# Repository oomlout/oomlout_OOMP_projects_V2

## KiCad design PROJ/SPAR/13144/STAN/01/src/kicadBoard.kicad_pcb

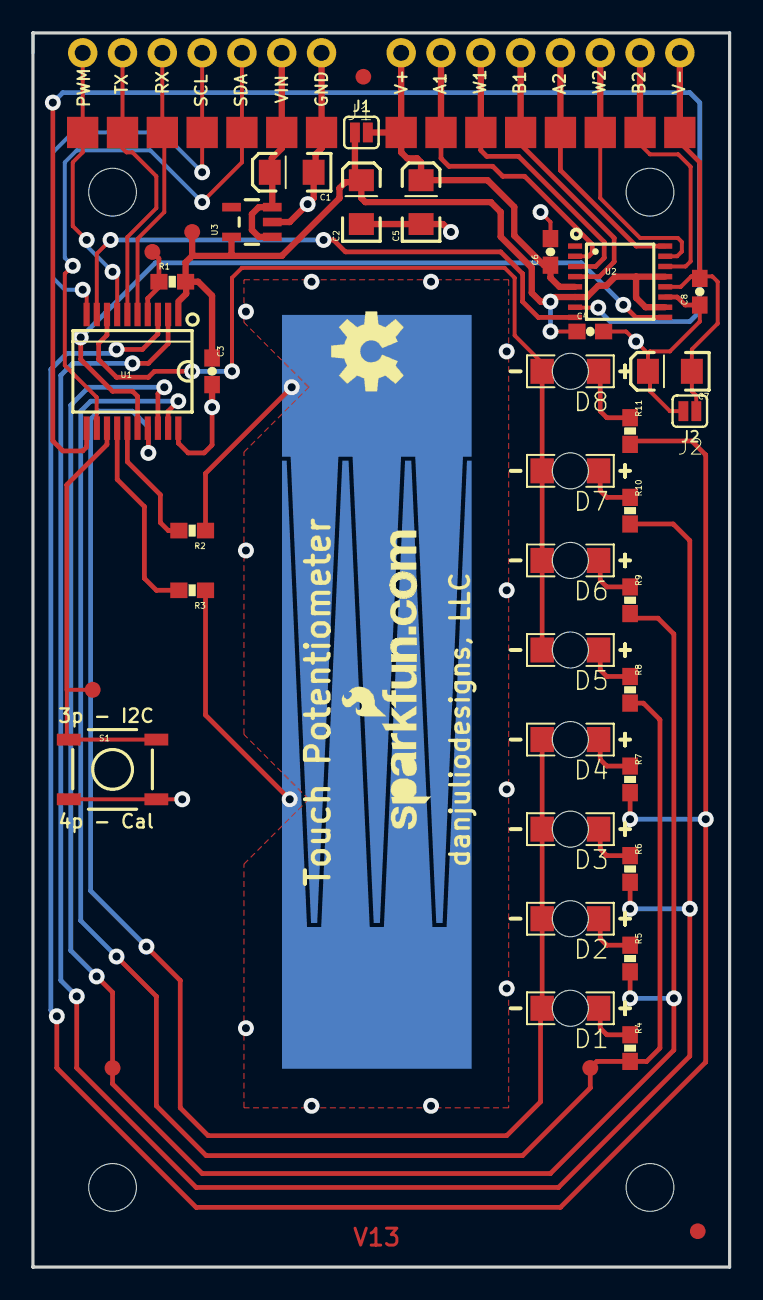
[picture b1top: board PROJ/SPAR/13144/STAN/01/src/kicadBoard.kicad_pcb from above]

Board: 2 copper layers, 44.5 x 78.7 mm, 78 parts (1 on the bottom side), 39 nets.

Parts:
C1, C2, C5, C7: 10uF; EIA3216
C3, C4, C6, C8: 0.1uF; 0603-CAP
D1, D2, D3, D4, D5, D6, D7, D8: Green; LED-1206-BOTTOM
FID1, FID2: FIDUCIAL1X2; FIDUCIAL-1X2
FRAME3: FRAME-LEDGER; CREATIVE_COMMONS
J1, J2: SJ_2S
JP1, JP2, JP3, JP4, JP5, JP6, JP7, JP8, JP9, JP10, JP11, JP12, JP13, JP14, JP15: 1X01NS
R1: 10K; 0603-RES
R2, R3, R4, R5, R6, R7, R8, R9, R10, R11: 100; 0603-RES
S1: TACTILE-SWITCH-SMD
STANDOFF1, STANDOFF2, STANDOFF3, STANDOFF4: STAND-OFFTIGHT; STAND-OFF-TIGHT
TP1, TP2, TP3, TP4, TP5: PAD.03X.04
TP6, TP7, TP8, TP9, TP10, TP11, TP12, TP13, TP14, TP15, TP16, TP17, TP18, TP19, TP20: 2MM_SMD_PAD
TS1: 2CH_48MM_LINEAR_TOUCH
U1: PIC16F1829; SSOP20
U2: AD5262; SSOP16
U3: 5V; SOT23-5
U$4: OSHW-LOGOM; OSHW-LOGO-M
U$5: SFE_LOGO_NAME_WEB; SFE-NEW-WEBLOGO

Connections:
+5V: C2.A, C3.1, C4.1, J1.1, R1.2, TP2.P$1, U1.1, U2.6, U2.10, U2.13, U3.5
A1: JP14.1, TP19.P$1, U2.2
A2: JP11.1, TP16.P$1, U2.16
AUX: S1.1, TP3.P$1, U1.13
B1: JP12.1, TP17.P$1, U2.4
B2: JP9.1, TP14.P$1, U2.14
CPAD1: R3.2, U1.14
CPAD2: R2.2, U1.15
CSN: U1.16, U2.9
GND: C1.C, C2.C, C3.2, C4.2, C5.C, C6.2, C7.A, C8.1, J2.1, JP7.1, S1.3, TP12.P$1, U1.20, U2.11, U3.2
LA0: R4.2, R8.2, TP4.P$1, U1.19
LA1: R5.2, R9.2, TP5.P$1, U1.18
LA2: R6.2, R10.2, U1.2
LA3: R7.2, R11.2, U1.3
LED_PWM1: D1.C, D2.C, D3.C, D4.C, U1.17
LED_PWM2: D5.C, D6.C, D7.C, D8.C, U1.8
unnamed: D1.A, R4.1
unnamed: D2.A, R5.1
unnamed: D3.A, R6.1
unnamed: D4.A, R7.1
unnamed: D5.A, R8.1
unnamed: D6.A, R9.1
unnamed: D7.A, R10.1
unnamed: D8.A, R11.1
unnamed: R2.1, TS1.P$2
unnamed: R3.1, TS1.P$1
PWM_OUT: JP3.1, TP8.P$1, U1.7
RX: JP4.1, TP9.P$1, U1.5
SCL: JP2.1, TP7.P$1, U1.10
SCLK: U1.11, U2.7
SDA: JP1.1, TP6.P$1, U1.12
SDO: U1.9, U2.8
TX: JP5.1, TP10.P$1, U1.6
V+: C5.A, C6.1, J1.2, JP15.1, TP20.P$1, U2.5
V-: C7.C, C8.2, J2.2, JP8.1, TP13.P$1, U2.12
VIN: C1.A, JP6.1, TP11.P$1, U3.1, U3.3
VPP: R1.1, TP1.P$1, U1.4
W1: JP13.1, TP18.P$1, U2.3
W2: JP10.1, TP15.P$1, U2.15

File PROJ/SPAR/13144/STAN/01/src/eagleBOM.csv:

"Part";"Value";"Device";"Package";"Description";"PROD_ID";"VALUE";
"C1";"10uF";"10UF-16V-10%(TANT)";"EIA3216";"CAP-00811";"CAP-00811";"10uF";
"C2";"10uF";"10UF-16V-10%(TANT)";"EIA3216";"CAP-00811";"CAP-00811";"10uF";
"C3";"0.1uF";"0.1UF-25V(+80/-20%)(0603)";"0603-CAP";"CAP-00810";"CAP-00810";"0.1uF";
"C4";"0.1uF";"0.1UF-25V(+80/-20%)(0603)";"0603-CAP";"CAP-00810";"CAP-00810";"0.1uF";
"C5";"10uF";"10UF-16V-10%(TANT)";"EIA3216";"CAP-00811";"CAP-00811";"10uF";
"C6";"0.1uF";"0.1UF-25V(+80/-20%)(0603)";"0603-CAP";"CAP-00810";"CAP-00810";"0.1uF";
"C7";"10uF";"10UF-16V-10%(TANT)";"EIA3216";"CAP-00811";"CAP-00811";"10uF";
"C8";"0.1uF";"0.1UF-25V(+80/-20%)(0603)";"0603-CAP";"CAP-00810";"CAP-00810";"0.1uF";
"D1";"Green";"LED-GREEN1206-BOTTOM";"LED-1206-BOTTOM";"Various green LEDs";"DIO-11076";"Green";
"D2";"Green";"LED-GREEN1206-BOTTOM";"LED-1206-BOTTOM";"Various green LEDs";"DIO-11076";"Green";
"D3";"Green";"LED-GREEN1206-BOTTOM";"LED-1206-BOTTOM";"Various green LEDs";"DIO-11076";"Green";
"D4";"Green";"LED-GREEN1206-BOTTOM";"LED-1206-BOTTOM";"Various green LEDs";"DIO-11076";"Green";
"D5";"Green";"LED-GREEN1206-BOTTOM";"LED-1206-BOTTOM";"Various green LEDs";"DIO-11076";"Green";
"D6";"Green";"LED-GREEN1206-BOTTOM";"LED-1206-BOTTOM";"Various green LEDs";"DIO-11076";"Green";
"D7";"Green";"LED-GREEN1206-BOTTOM";"LED-1206-BOTTOM";"Various green LEDs";"DIO-11076";"Green";
"D8";"Green";"LED-GREEN1206-BOTTOM";"LED-1206-BOTTOM";"Various green LEDs";"DIO-11076";"Green";
"FID1";"FIDUCIAL1X2";"FIDUCIAL1X2";"FIDUCIAL-1X2";"Fiducial Alignment Points";"";"";
"FID2";"FIDUCIAL1X2";"FIDUCIAL1X2";"FIDUCIAL-1X2";"Fiducial Alignment Points";"";"";
"FRAME3";"FRAME-LEDGER";"FRAME-LEDGER";"CREATIVE_COMMONS";"Schematic Frame";"";"";
"J1";"";"SJCLOSED";"SJ_2S";"Solder jumper";"";"";
"J2";"";"SJCLOSED";"SJ_2S";"Solder jumper";"";"";
"JP1";"";"M01SMDNS";"1X01NS";"Header 1";"";"";
"JP2";"";"M01SMDNS";"1X01NS";"Header 1";"";"";
"JP3";"";"M01SMDNS";"1X01NS";"Header 1";"";"";
"JP4";"";"M01SMDNS";"1X01NS";"Header 1";"";"";
"JP5";"";"M01SMDNS";"1X01NS";"Header 1";"";"";
"JP6";"";"M01SMDNS";"1X01NS";"Header 1";"";"";
"JP7";"";"M01SMDNS";"1X01NS";"Header 1";"";"";
"JP8";"";"M01SMDNS";"1X01NS";"Header 1";"";"";
"JP9";"";"M01SMDNS";"1X01NS";"Header 1";"";"";
"JP10";"";"M01SMDNS";"1X01NS";"Header 1";"";"";
"JP11";"";"M01SMDNS";"1X01NS";"Header 1";"";"";
"JP12";"";"M01SMDNS";"1X01NS";"Header 1";"";"";
"JP13";"";"M01SMDNS";"1X01NS";"Header 1";"";"";
"JP14";"";"M01SMDNS";"1X01NS";"Header 1";"";"";
"JP15";"";"M01SMDNS";"1X01NS";"Header 1";"";"";
"R1";"10K";"10KOHM-1/10W-1%(0603)0603";"0603-RES";"RES-00824";"RES-00824";"10K";
"R2";"100";"100OHM-1/10W-1%(0603)";"0603-RES";"RES-07863";"RES-07863";"100";
"R3";"100";"100OHM-1/10W-1%(0603)";"0603-RES";"RES-07863";"RES-07863";"100";
"R4";"100";"100OHM-1/10W-1%(0603)";"0603-RES";"RES-07863";"RES-07863";"100";
"R5";"100";"100OHM-1/10W-1%(0603)";"0603-RES";"RES-07863";"RES-07863";"100";
"R6";"100";"100OHM-1/10W-1%(0603)";"0603-RES";"RES-07863";"RES-07863";"100";
"R7";"100";"100OHM-1/10W-1%(0603)";"0603-RES";"RES-07863";"RES-07863";"100";
"R8";"100";"100OHM-1/10W-1%(0603)";"0603-RES";"RES-07863";"RES-07863";"100";
"R9";"100";"100OHM-1/10W-1%(0603)";"0603-RES";"RES-07863";"RES-07863";"100";
"R10";"100";"100OHM-1/10W-1%(0603)";"0603-RES";"RES-07863";"RES-07863";"100";
"R11";"100";"100OHM-1/10W-1%(0603)";"0603-RES";"RES-07863";"RES-07863";"100";
"S1";"";"SWITCH-MOMENTARY-2SMD";"TACTILE-SWITCH-SMD";"Various NO switches- pushbuttons, reed, etc";"SWCH-08247";"";
"STANDOFF1";"STAND-OFFTIGHT";"STAND-OFFTIGHT";"STAND-OFF-TIGHT";"#4 Stand Off";"";"";
"STANDOFF2";"STAND-OFFTIGHT";"STAND-OFFTIGHT";"STAND-OFF-TIGHT";"#4 Stand Off";"";"";
"STANDOFF3";"STAND-OFFTIGHT";"STAND-OFFTIGHT";"STAND-OFF-TIGHT";"#4 Stand Off";"";"";
"STANDOFF4";"STAND-OFFTIGHT";"STAND-OFFTIGHT";"STAND-OFF-TIGHT";"#4 Stand Off";"";"";
"TP1";"";"TEST-POINT3X4";"PAD.03X.04";"Bare copper test points for troubleshooting or ICT";"";"";
"TP2";"";"TEST-POINT3X4";"PAD.03X.04";"Bare copper test points for troubleshooting or ICT";"";"";
"TP3";"";"TEST-POINT3X4";"PAD.03X.04";"Bare copper test points for troubleshooting or ICT";"";"";
"TP4";"";"TEST-POINT3X4";"PAD.03X.04";"Bare copper test points for troubleshooting or ICT";"";"";
"TP5";"";"TEST-POINT3X4";"PAD.03X.04";"Bare copper test points for troubleshooting or ICT";"";"";
"TP6";"";"SINGLE_PADSMD";"2MM_SMD_PAD";"";"";"";
"TP7";"";"SINGLE_PADSMD";"2MM_SMD_PAD";"";"";"";
"TP8";"";"SINGLE_PADSMD";"2MM_SMD_PAD";"";"";"";
"TP9";"";"SINGLE_PADSMD";"2MM_SMD_PAD";"";"";"";
"TP10";"";"SINGLE_PADSMD";"2MM_SMD_PAD";"";"";"";
"TP11";"";"SINGLE_PADSMD";"2MM_SMD_PAD";"";"";"";
"TP12";"";"SINGLE_PADSMD";"2MM_SMD_PAD";"";"";"";
"TP13";"";"SINGLE_PADSMD";"2MM_SMD_PAD";"";"";"";
"TP14";"";"SINGLE_PADSMD";"2MM_SMD_PAD";"";"";"";
"TP15";"";"SINGLE_PADSMD";"2MM_SMD_PAD";"";"";"";
"TP16";"";"SINGLE_PADSMD";"2MM_SMD_PAD";"";"";"";
"TP17";"";"SINGLE_PADSMD";"2MM_SMD_PAD";"";"";"";
"TP18";"";"SINGLE_PADSMD";"2MM_SMD_PAD";"";"";"";
"TP19";"";"SINGLE_PADSMD";"2MM_SMD_PAD";"";"";"";
"TP20";"";"SINGLE_PADSMD";"2MM_SMD_PAD";"";"";"";
"TS1";"";"2CH_LINEAR_TOUCH";"2CH_48MM_LINEAR_TOUCH";"";"";"";
"U$4";"OSHW-LOGOM";"OSHW-LOGOM";"OSHW-LOGO-M";"Open Source Hardware Logo This logo indicates the piece of hardware it is found on incorporates a OSHW license and/or adheres to the definition of open source hardware found here: http://freedomdefined.org/OSHW";"";"";
"U$5";"SFE_LOGO_NAME_WEB";"SFE_LOGO_NAME_WEB";"SFE-NEW-WEBLOGO";"SparkFun.com board silk.";"";"";
"U1";"PIC16F1829";"PIC16F1829";"SSOP20";"";"IC-12357";"";
"U2";"AD5262";"AD5262";"SSOP16";"";"IC-12358";"";
"U3";"5V";"V_REG_MIC52055V";"SOT23-5";"V_REG MIC5219";"VREG-00823";"5V";

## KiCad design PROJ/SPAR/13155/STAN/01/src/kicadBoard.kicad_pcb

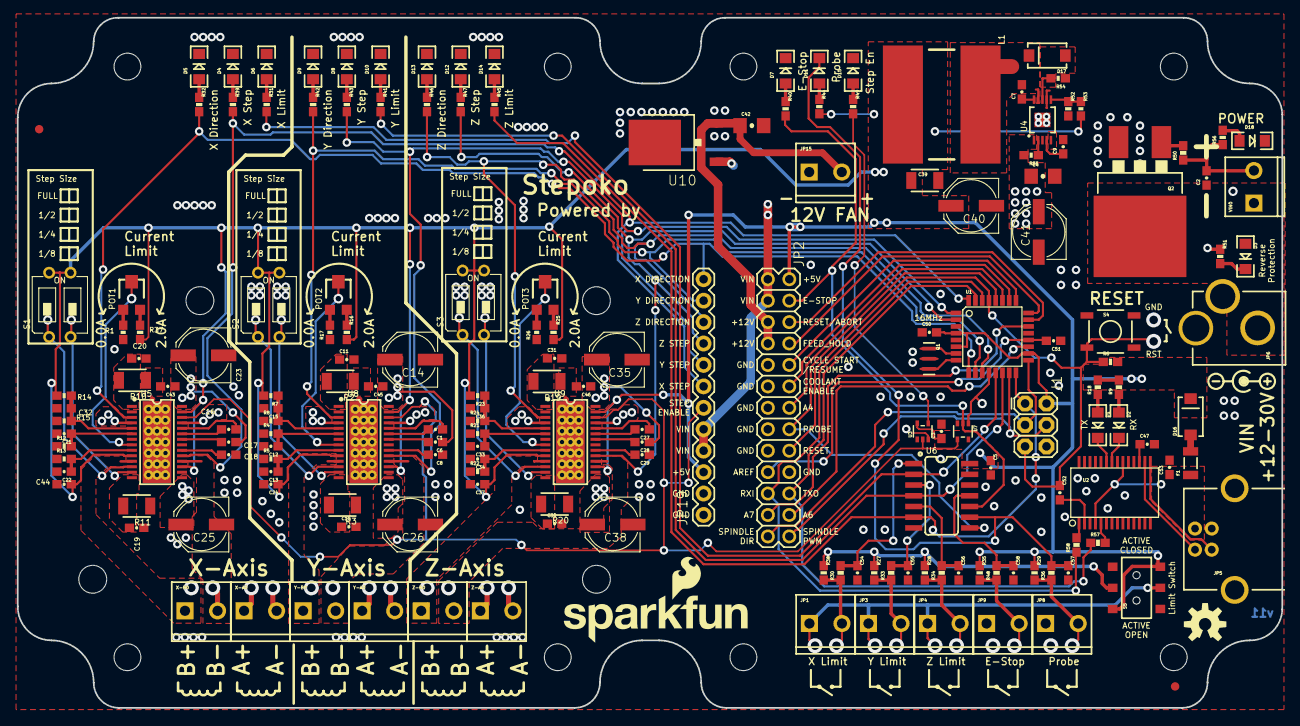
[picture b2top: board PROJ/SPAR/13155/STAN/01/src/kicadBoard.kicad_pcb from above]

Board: 2 copper layers, 149.9 x 81.8 mm, 184 parts (1 on the bottom side), 133 nets.

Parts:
C1, C6, C8, C16, C17, C18, C27, C28, C29: 0.22uF; 0603-CAP
C2, C3, C5, C7, C10, C11, C19, C20, C24, C30, C31, C37, C43, C44, C45, C46, C47, C50, C51, C52, C53, C54, C55, C56, C57, C58: 0.1uF; 0603-CAP
C4, C42: 1.0uF; 1206-CAP
C9: 10nF; 0603-CAP
C12, C13, C21, C22, C33, C34: 1nF; 0603-CAP
C14, C23, C25, C26, C35, C38, C40, C41: 47uF; PANASONIC_D
C15, C32, C36: 0.18uF; 0603
C39: 22uF; 1210
D1, D3, D5, D7, D9, D13: RED; LED-1206
D2, D4, D8, D12, D15: GREEN; LED-1206
D6, D10, D14: Yellow; LED-1206
D11, D18: BLUE; LED-1206
D16, D17: MBRA140; SMA-DIODE
F1: PTCSMD; PTC-1206
FID1, FID2: FIDUCIAL1X2; FIDUCIAL-1X2
FRAME1, FRAME2: FRAME-LEDGER; CREATIVE_COMMONS
J1: AVR ISP; 2X3
JP1, JP3, JP4, JP8, JP9, JP15: 3.5mm; SCREWTERMINAL-3.5MM-2_LOCK
JP2: 2X13
JP5: USB-B; USB-B-PTH
JP6: POWER; POWER_JACK_PTH_LOCK
JP19: 1X12
L1: 27uH; INDUCTOR_SDR1307
LOGO1: OSHW-LOGOM; OSHW-LOGO-M
LOGO2: SFE_LOGO_NAME_FLAME.2_INCH; SFE_LOGO_NAME_FLAME_.2@1
LOGO3: SFE_LOGO_NAME_FLAME.2_INCH; SFE_LOGO_NAME_FLAME_.2
POT1, POT2, POT3: 10K_LINEAR_POT_SMD; TC33X
Q1: 16MHZ; RESONATOR-SMD
Q2: 100A/100V; TO-263_D2PAK
R1, R17, R26: 0; 0603
R2, R3, R10, R11, R19, R20: 0.1; 1210
R4, R5, R12, R13, R21, R22: 39K; 0603
R6, R16, R25, R27, R28, R29, R35, R37, R38, R51, R52, R56: 10K; 0603-RES
R7, R8, R14, R15, R23, R24: 5.6K; 0603
R9, R18, R30, R33, R34, R36, R48, R50, R57, R58: 1K; 0603-RES@1
R31, R32, R39, R40, R41, R42, R43, R44, R45, R46, R47, R49: 1K; 0603-RES
R53: 9.76K; 0603
R54: 50.0m; 0603
R55: 348K; 0603
S1, S2, S3: 2-POS-DIPCTS-THRU-HOLE; 209-2LPST
S4: Reset; TACTILE-SWITCH-SMD
S5: DPDT; AYZ0202
U1: ATMEGA328; TQFP32-08@1
U2: FT232RLSSOP; SSOP28DB
U3: 74LVC1G04; SOT353
U4: LM25011; HVSS0P-10
U5, U8, U9: DRV8811; HTSSOP28
U6: 74HC7014D; SOIC-14
U7: 7432SE; SOT353
U10: +12v; TO-252
U$1: FLANGED_RED_ENCLOSURE-DIMENSION-NO-INNER-HOLES
U$2, U$3, U$4, U$5: STAND-OFF
VIN0: 3.5mm; SCREWTERMINAL-3.5MM-2_LOCK
X-A0: 3.5mm; SCREWTERMINAL-3.5MM-2_LOCK
X-B0: 3.5mm; SCREWTERMINAL-3.5MM-2_LOCK
Y-A0: 3.5mm; SCREWTERMINAL-3.5MM-2_LOCK
Y-B0: 3.5mm; SCREWTERMINAL-3.5MM-2_LOCK
Z-A0: 3.5mm; SCREWTERMINAL-3.5MM-2_LOCK
Z-B0: 3.5mm; SCREWTERMINAL-3.5MM-2_LOCK

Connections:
5V: C3.1, C5.1, C24.1, C37.1, C39.1, C40.+, C44.1, C50.2, D16.C, J1.2, JP2.2, JP19.3, L1.P$2, R6.2, R7.2, R9.2, R14.2, R16.2, R18.2, R23.2, R25.2, R29.1, R35.1, R37.2, R44.2, R53.2, S1.3, S1.4, S2.3, S2.4, S3.3, S3.4, S5.1, S5.6, U1.4, U1.6, U1.18, U3.5, U5.10, U5.17, U5.27, U6.14, U7.5, U8.10, U8.17, U8.27, U9.10, U9.17, U9.27
A0-RESET/ABORT: JP2.6, U1.23
A1-FEED_HOLD: JP2.8, U1.24
A2-CYCLE_START/RESUME: JP2.10, U1.25
A3-COOLANT_ENABLE: JP2.12, U1.26
A4: JP2.14, U1.27
A5-PROBE: JP2.16, U1.28, U6.8
A6: JP2.24, U1.19
A7: JP2.23, U1.22
AREF: C51.2, JP2.19, U1.20
D2-STEP-X: JP19.7, R39.2, U1.32, U5.19
D3-STEP-Y: JP19.8, R43.2, U1.1, U8.19
D4-STEP-Z: JP19.9, R47.2, U1.2, U9.19
D5-DIR-X: JP19.12, R32.2, U1.9, U5.3
D6-DIR-Y: JP19.11, R42.2, U1.10, U8.3
D7-DIR-Z: JP19.10, R46.2, U1.11, U9.3
D8-STEP_EN: U1.12, U7.1
D9-LIM-X: R31.2, U1.13, U6.2
D10-LIM-Y: R41.2, U1.14, U6.4
D+: JP5.D+, U2.15
D-: JP5.D-, U2.16
DTR: C52.2, U2.2
ESTOP: C58.1, R48.2, U6.11
ESTOP-LOGIC: JP2.4, R40.2, U6.10, U7.2
GND: C3.2, C4.2, C5.2, C8.1, C9.2, C10.2, C11.2, C12.2, C13.2, C14.-, C15.2, C18.1, C19.2, C20.2, C21.2, C22.2, C23.-, C24.2, C25.-, C26.-, C29.1, C30.2, C31.2, C32.2, C33.2, C34.2, C35.-, C36.2, C37.2, C38.-, C39.2, C40.-, C41.-, C42.2, C43.2, C44.2, C45.2, C46.2, C47.2, C50.1, C51.1, C53.2, C54.2, C55.2, C56.2, C57.2, C58.2, D4.C, D5.C, D6.C, D7.C, D8.C, D9.C, D10.C, D12.C, D13.C, D14.C, D15.C, D18.C, J1.6, JP2.9, JP2.11, JP2.13, JP2.15, JP2.17, JP2.20, JP5.GND, JP8.1, JP9.1, JP15.1, JP19.1, JP19.2, Q1.2, Q2.3, R1.1, R2.1, R3.1, R4.1, R5.1, R8.1, R10.1, R11.1, R12.1, R13.1, R15.1, R17.1, R19.1, R20.1, R21.1, R22.1, R24.1, R26.1, R52.2, R54.1, S4.1, S5.3, S5.4, U1.3, U1.5, U1.21, U2.7, U2.18, U2.21, U2.25, U2.26, U3.3, U4.5, U4.7, U4.PAD, U5.7, U5.16, U5.21, U5.GND@10, U5.GND@11, U5.GND@12, U5.GND@13, U5.GND@14, U5.GND@15, U5.GND@16, U5.GND@17, U5.GND@18, U5.GND@19, U5.GND@20, U5.GND@21, U5.GND@22, U5.GND@23, U5.GND@24, U5.GND@25, U5.GND@26, U5.GND@27, U5.GND@28, U5.GND@29, U5.GND@30, U5.GND@PAD, U6.7, U6.13, U7.3, U8.7, U8.16, U8.21, U8.GND@10, U8.GND@11, U8.GND@12, U8.GND@13, U8.GND@14, U8.GND@15, U8.GND@16, U8.GND@17, U8.GND@18, U8.GND@19, U8.GND@20, U8.GND@21, U8.GND@22, U8.GND@23, U8.GND@24, U8.GND@25, U8.GND@26, U8.GND@27, U8.GND@28, U8.GND@29, U8.GND@30, U8.GND@PAD, U9.7, U9.16, U9.21, U9.GND@10, U9.GND@11, U9.GND@12, U9.GND@13, U9.GND@14, U9.GND@15, U9.GND@16, U9.GND@17, U9.GND@18, U9.GND@19, U9.GND@20, U9.GND@21, U9.GND@22, U9.GND@23, U9.GND@24, U9.GND@25, U9.GND@26, U9.GND@27, U9.GND@28, U9.GND@29, U9.GND@30, U9.GND@PAD, U10.3
MISO-D12-LIMIT-Z: J1.1, R45.2, U1.16, U6.6
MOSI-D11-SPINDLE_PWM: J1.4, JP2.26, U1.15
unnamed: R58.2, U2.1
unnamed: D2.A, R9.1
unnamed: D1.A, R18.1
unnamed: JP1.1, JP3.1, JP4.1, S5.5
unnamed: D7.A, R40.1
unnamed: Q1.3, U1.8
unnamed: JP1.2, R30.1, R38.2
unnamed: Q1.1, U1.7
unnamed: POT1.3, R37.1
unnamed: POT1.1, R1.2
unnamed: C12.1, R4.2, U8.6
unnamed: C13.1, R5.2, U8.9
unnamed: D11.A, R44.1
unnamed: C15.1, R7.1, R8.2, U8.5
unnamed: S2.2, U8.13
unnamed: D15.A, R49.1
unnamed: C2.1, D3.A, JP6.GND, Q2.2, VIN0.1
unnamed: D6.A, R31.1
unnamed: D5.A, R32.1
unnamed: D4.A, R39.1
unnamed: R52.1, R53.1, U4.6
unnamed: D10.A, R41.1
unnamed: S2.1, U8.12
unnamed: C16.1, U5.24
unnamed: C16.2, U5.23
unnamed: C8.2, U8.20
unnamed: POT2.2, U8.8
unnamed: C21.1, R12.2, U5.6
unnamed: C22.1, R13.2, U5.9
unnamed: C32.1, R14.1, R15.2, U5.5
unnamed: D9.A, R42.1
unnamed: D1.C, U2.23
unnamed: D2.C, U2.22
unnamed: S1.2, U5.13
unnamed: S1.1, U5.12
unnamed: D8.A, R43.1
unnamed: U5.11, X-B0.1
unnamed: C18.2, U5.20
unnamed: Q2.1, R50.2
unnamed: D14.A, R45.1
unnamed: D3.C, R51.2
unnamed: JP3.2, R27.2, R33.1
unnamed: JP4.2, R28.2, R34.1
unnamed: POT2.3, R16.1
unnamed: POT2.1, R17.2
unnamed: C6.2, U8.22
unnamed: C1.1, U8.24
unnamed: C1.2, U8.23
unnamed: U8.11, Y-B0.1
unnamed: D16.A, F1.2
unnamed: JP8.2, R29.2, R36.1
unnamed: U8.18, Y-B0.2
unnamed: U8.4, Y-A0.1
unnamed: JP9.2, R35.2, R48.1
unnamed: U8.25, Y-A0.2
unnamed: C10.1, R3.2, U8.14
unnamed: D18.A, R56.2
unnamed: D13.A, R46.1
unnamed: D12.A, R47.1
unnamed: R57.2, U2.5
unnamed: R55.1, U4.2
unnamed: C17.2, U5.22
unnamed: C7.1, U4.10
unnamed: U5.18, X-B0.2
unnamed: C7.2, D17.C, L1.P$1, U4.9
unnamed: U5.4, X-A0.1
unnamed: C11.1, R2.2, U8.1
unnamed: C33.1, R21.2, U9.6
unnamed: C34.1, R22.2, U9.9
unnamed: C36.1, R23.1, R24.2, U9.5
unnamed: S3.2, U9.13
unnamed: S3.1, U9.12
unnamed: C9.1, U4.4
unnamed: U5.25, X-A0.2
unnamed: C29.2, U9.20
unnamed: POT3.2, U9.8
unnamed: POT3.3, R25.1
unnamed: POT3.1, R26.2
unnamed: C28.2, U9.22
unnamed: C27.1, U9.24
unnamed: C27.2, U9.23
unnamed: U9.11, Z-B0.1
unnamed: U9.18, Z-B0.2
unnamed: U9.4, Z-A0.1
unnamed: U9.25, Z-A0.2
unnamed: C30.1, R20.2, U9.14
unnamed: C19.1, R11.2, U5.14
unnamed: C31.1, R19.2, U9.1
unnamed: POT1.2, U5.8
unnamed: R27.1, R28.1, R38.1, S5.2
unnamed: C20.1, R10.2, U5.1
unnamed: D17.A, R54.2, U4.8
unnamed: C47.1, U2.17
PROBE: C57.1, D11.C, R36.2, U6.9
RESET: C52.1, J1.5, JP2.18, R6.1, S4.3, U1.29
RXI: JP2.21, R58.1, U1.30
SCK-D13-SPINDLE_DIR: J1.3, JP2.25, U1.17
STEP-EN_LED: R49.2, U3.4
STEP_ENABLE: JP19.6, U3.2, U5.26, U7.4, U8.26, U9.26
TXO: JP2.22, R57.1, U1.31
VCC: C42.1, JP2.5, JP2.7, JP15.2, U10.2
VCC_USB: C53.1, F1.1, JP5.VBUS, U2.4, U2.20
VIN: C2.2, C4.1, C6.1, C14.+, C17.1, C23.+, C25.+, C26.+, C28.1, C35.+, C38.+, C41.+, C43.1, C45.1, C46.1, JP2.1, JP2.3, JP6.PWR, JP19.4, JP19.5, R50.1, R51.1, R55.2, R56.1, U4.1, U5.15, U5.28, U8.15, U8.28, U9.15, U9.28, U10.1, VIN0.2
X_LIM: C54.1, R30.2, U6.1
Y_LIM: C55.1, R33.2, U6.3
Z_LIM: C56.1, R34.2, U6.5

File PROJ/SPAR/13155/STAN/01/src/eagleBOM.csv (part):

"Part";"Value";"Device";"Package";"Description";"DESIGNER";"PROD_ID";"SF_ID";"VALUE";"VERSION";
"C1";"0.22uF";"0.22UF50V-20%,+80%(0603)";"0603-CAP";"CAP-09885";"";"CAP-09885";"";"0.22uF";"";
"C2";"0.1uF";"0.1UF-100V-10%(0603)";"0603-CAP";"CAP-08390";"";"CAP-08390";"";"0.1uF";"";
"C3";"0.1uF";"0.1UF-25V(+80/-20%)(0603)";"0603-CAP";"CAP-00810";"";"CAP-00810";"";"0.1uF";"";
"C4";"1.0uF";"1.0UF50V10%(1206)";"1206-CAP";"CAP-09822";"";"";"";"";"";
"C5";"0.1uF";"0.1UF-25V(+80/-20%)(0603)";"0603-CAP";"CAP-00810";"";"CAP-00810";"";"0.1uF";"";
"C6";"0.22uF";"0.22UF50V-20%,+80%(0603)";"0603-CAP";"CAP-09885";"";"CAP-09885";"";"0.22uF";"";
"C7";"0.1uF";"0.1UF-25V(+80/-20%)(0603)";"0603-CAP";"CAP-00810";"";"CAP-00810";"";"0.1uF";"";
"C8";"0.22uF";"0.22UF50V-20%,+80%(0603)";"0603-CAP";"CAP-09885";"";"CAP-09885";"";"0.22uF";"";
"C9";"10nF";"10NF/10000PF-50V-10%(0603)";"0603-CAP";"CAP-00867";"";"CAP-00867";"";"10nF";"";
"C10";"0.1uF";"0.1UF-25V(+80/-20%)(0603)";"0603-CAP";"CAP-00810";"";"CAP-00810";"";"0.1uF";"";
"C11";"0.1uF";"0.1UF-25V(+80/-20%)(0603)";"0603-CAP";"CAP-00810";"";"CAP-00810";"";"0.1uF";"";
"C12";"1nF";"1NF/1000PF-50V-10%(0603)";"0603-CAP";"CAP-07886";"";"CAP-07886";"";"1nF";"";
"C13";"1nF";"1NF/1000PF-50V-10%(0603)";"0603-CAP";"CAP-07886";"";"CAP-07886";"";"1nF";"";
"C14";"47uF";"47UF-50V-20%(ELECT)";"PANASONIC_D";"CAP-10547";"";"CAP-10547";"";"";"";
"C15";"0.18uF";"0.18UF-10V(+-10%)(0603)";"0603";"";"";"CAP-12380";"";"";"";
"C16";"0.22uF";"0.22UF50V-20%,+80%(0603)";"0603-CAP";"CAP-09885";"";"CAP-09885";"";"0.22uF";"";
"C17";"0.22uF";"0.22UF50V-20%,+80%(0603)";"0603-CAP";"CAP-09885";"";"CAP-09885";"";"0.22uF";"";
"C18";"0.22uF";"0.22UF50V-20%,+80%(0603)";"0603-CAP";"CAP-09885";"";"CAP-09885";"";"0.22uF";"";
"C19";"0.1uF";"0.1UF-25V(+80/-20%)(0603)";"0603-CAP";"CAP-00810";"";"CAP-00810";"";"0.1uF";"";
"C20";"0.1uF";"0.1UF-25V(+80/-20%)(0603)";"0603-CAP";"CAP-00810";"";"CAP-00810";"";"0.1uF";"";
"C21";"1nF";"1NF/1000PF-50V-10%(0603)";"0603-CAP";"CAP-07886";"";"CAP-07886";"";"1nF";"";
"C22";"1nF";"1NF/1000PF-50V-10%(0603)";"0603-CAP";"CAP-07886";"";"CAP-07886";"";"1nF";"";
"C23";"47uF";"47UF-50V-20%(ELECT)";"PANASONIC_D";"CAP-10547";"";"CAP-10547";"";"";"";
"C24";"0.1uF";"0.1UF-25V(+80/-20%)(0603)";"0603-CAP";"CAP-00810";"";"CAP-00810";"";"0.1uF";"";
"C25";"47uF";"47UF-50V-20%(ELECT)";"PANASONIC_D";"CAP-10547";"";"CAP-10547";"";"";"";
"C26";"47uF";"47UF-50V-20%(ELECT)";"PANASONIC_D";"CAP-10547";"";"CAP-10547";"";"";"";
"C27";"0.22uF";"0.22UF50V-20%,+80%(0603)";"0603-CAP";"CAP-09885";"";"CAP-09885";"";"0.22uF";"";
"C28";"0.22uF";"0.22UF50V-20%,+80%(0603)";"0603-CAP";"CAP-09885";"";"CAP-09885";"";"0.22uF";"";
"C29";"0.22uF";"0.22UF50V-20%,+80%(0603)";"0603-CAP";"CAP-09885";"";"CAP-09885";"";"0.22uF";"";
"C30";"0.1uF";"0.1UF-25V(+80/-20%)(0603)";"0603-CAP";"CAP-00810";"";"CAP-00810";"";"0.1uF";"";
"C31";"0.1uF";"0.1UF-25V(+80/-20%)(0603)";"0603-CAP";"CAP-00810";"";"CAP-00810";"";"0.1uF";"";
"C32";"0.18uF";"0.18UF-10V(+-10%)(0603)";"0603";"";"";"CAP-12380";"";"";"";
"C33";"1nF";"1NF/1000PF-50V-10%(0603)";"0603-CAP";"CAP-07886";"";"CAP-07886";"";"1nF";"";
"C34";"1nF";"1NF/1000PF-50V-10%(0603)";"0603-CAP";"CAP-07886";"";"CAP-07886";"";"1nF";"";
"C35";"47uF";"47UF-50V-20%(ELECT)";"PANASONIC_D";"CAP-10547";"";"CAP-10547";"";"";"";
"C36";"0.18uF";"0.18UF-10V(+-10%)(0603)";"0603";"";"";"CAP-12380";"";"";"";
"C37";"0.1uF";"0.1UF-25V(+80/-20%)(0603)";"0603-CAP";"CAP-00810";"";"CAP-00810";"";"0.1uF";"";
"C38";"47uF";"47UF-50V-20%(ELECT)";"PANASONIC_D";"CAP-10547";"";"CAP-10547";"";"";"";
"C39";"22uF";"22UF-16V-20%-(1210)";"1210";"CAP-10381";"";"CAP-10381";"";"22uF";"";
"C40";"47uF";"47UF-50V-20%(ELECT)";"PANASONIC_D";"CAP-10547";"";"CAP-10547";"";"";"";
"C41";"47uF";"47UF-50V-20%(ELECT)";"PANASONIC_D";"CAP-10547";"";"CAP-10547";"";"";"";
"C42";"1.0uF";"1.0UF50V10%(1206)";"1206-CAP";"CAP-09822";"";"";"";"";"";
"C43";"0.1uF";"0.1UF-100V-10%(0603)";"0603-CAP";"CAP-08390";"";"CAP-08390";"";"0.1uF";"";
"C44";"0.1uF";"0.1UF-25V(+80/-20%)(0603)";"0603-CAP";"CAP-00810";"";"CAP-00810";"";"0.1uF";"";
"C45";"0.1uF";"0.1UF-100V-10%(0603)";"0603-CAP";"CAP-08390";"";"CAP-08390";"";"0.1uF";"";
"C46";"0.1uF";"0.1UF-100V-10%(0603)";"0603-CAP";"CAP-08390";"";"CAP-08390";"";"0.1uF";"";
"C47";"0.1uF";"0.1UF-25V(+80/-20%)(0603)";"0603-CAP";"CAP-00810";"";"CAP-00810";"";"0.1uF";"";
"C50";"0.1uF";"0.1UF-25V(+80/-20%)(0603)";"0603-CAP";"CAP-00810";"";"CAP-00810";"";"0.1uF";"";
"C51";"0.1uF";"0.1UF-25V(+80/-20%)(0603)";"0603-CAP";"CAP-00810";"";"CAP-00810";"";"0.1uF";"";
"C52";"0.1uF";"0.1UF-25V(+80/-20%)(0603)";"0603-CAP";"CAP-00810";"";"CAP-00810";"";"0.1uF";"";
"C53";"0.1uF";"0.1UF-25V(+80/-20%)(0603)";"0603-CAP";"CAP-00810";"";"CAP-00810";"";"0.1uF";"";
"C54";"0.1uF";"0.1UF-25V(+80/-20%)(0603)";"0603-CAP";"CAP-00810";"";"CAP-00810";"";"0.1uF";"";
"C55";"0.1uF";"0.1UF-25V(+80/-20%)(0603)";"0603-CAP";"CAP-00810";"";"CAP-00810";"";"0.1uF";"";
"C56";"0.1uF";"0.1UF-25V(+80/-20%)(0603)";"0603-CAP";"CAP-00810";"";"CAP-00810";"";"0.1uF";"";
"C57";"0.1uF";"0.1UF-25V(+80/-20%)(0603)";"0603-CAP";"CAP-00810";"";"CAP-00810";"";"0.1uF";"";
"C58";"0.1uF";"0.1UF-25V(+80/-20%)(0603)";"0603-CAP";"CAP-00810";"";"CAP-00810";"";"0.1uF";"";
"D1";"RED";"LED-REDLILYPAD";"LED-1206";"Assorted Red LEDs";"";"DIO-09912";"";"RED";"";
"D2";"GREEN";"LED-GREENLILYPAD";"LED-1206";"Various green LEDs";"";"DIO-09910";"";"GREEN";"";
"D3";"RED";"LED-REDLILYPAD";"LED-1206";"Assorted Red LEDs";"";"DIO-09912";"";"RED";"";
"D4";"GREEN";"LED-GREENLILYPAD";"LED-1206";"Various green LEDs";"";"DIO-09910";"";"GREEN";"";
"D5";"RED";"LED-REDLILYPAD";"LED-1206";"Assorted Red LEDs";"";"DIO-09912";"";"RED";"";
"D6";"Yellow";"LED-YELLOWLILYPAD";"LED-1206";"Yellow SMD LEDs";"";"DIO-09909";"";"Yellow";"";
"D7";"RED";"LED-REDLILYPAD";"LED-1206";"Assorted Red LEDs";"";"DIO-09912";"";"RED";"";
"D8";"GREEN";"LED-GREENLILYPAD";"LED-1206";"Various green LEDs";"";"DIO-09910";"";"GREEN";"";
"D9";"RED";"LED-REDLILYPAD";"LED-1206";"Assorted Red LEDs";"";"DIO-09912";"";"RED";"";
"D10";"Yellow";"LED-YELLOWLILYPAD";"LED-1206";"Yellow SMD LEDs";"";"DIO-09909";"";"Yellow";"";
"D11";"BLUE";"LED-BLUE1206";"LED-1206";"Blue LEDs for production use";"";"DIO-09911";"";"BLUE";"";
"D12";"GREEN";"LED-GREENLILYPAD";"LED-1206";"Various green LEDs";"";"DIO-09910";"";"GREEN";"";
"D13";"RED";"LED-REDLILYPAD";"LED-1206";"Assorted Red LEDs";"";"DIO-09912";"";"RED";"";
"D14";"Yellow";"LED-YELLOWLILYPAD";"LED-1206";"Yellow SMD LEDs";"";"DIO-09909";"";"Yellow";"";
"D15";"GREEN";"LED-GREENLILYPAD";"LED-1206";"Various green LEDs";"";"DIO-09910";"";"GREEN";"";
"D16";"MBRA140";"DIODE-SCHOTTKY-MBRA140";"SMA-DIODE";"Schottky diodes in SFE's production catalog";"";"DIO-08053";"";"MBRA140";"";
"D17";"MBRA140";"DIODE-SCHOTTKY-MBRA140";"SMA-DIODE";"Schottky diodes in SFE's production catalog";"";"DIO-08053";"";"MBRA140";"";
"D18";"BLUE";"LED-BLUE1206";"LED-1206";"Blue LEDs for production use";"";"DIO-09911";"";"BLUE";"";
"F1";"PTCSMD";"PTCSMD";"PTC-1206";"Resettable Fuse PTC";"";"RES-11150";"";"";"";
"FID1";"FIDUCIAL1X2";"FIDUCIAL1X2";"FIDUCIAL-1X2";"Fiducial Alignment Points";"";"";"";"";"";
"FID2";"FIDUCIAL1X2";"FIDUCIAL1X2";"FIDUCIAL-1X2";"Fiducial Alignment Points";"";"";"";"";"";
"FRAME1";"FRAME-LEDGER";"FRAME-LEDGER";"CREATIVE_COMMONS";"Schematic Frame";"Casey Kuhns";"";"";"";"v02";
"FRAME2";"FRAME-LEDGER";"FRAME-LEDGER";"CREATIVE_COMMONS";"Schematic Frame";"Casey Kuhns";"";"";"";"v02";
"J1";"AVR ISP";"AVR_SPI_PRG_6PTH";"2X3";"AVR ISP 6 Pin";"";"";"";"";"";
"JP1";"3.5mm";"M023.5MM_LOCK";"SCREWTERMINAL-3.5MM-2_LOCK";"Standard 2-pin 0.1" header. Use with";"";"CONN-08399";"";"";"";
"JP2";"";"M13X22X13";"2X13";"0.1" spaced headers";"";"";"";"";"";
"JP3";"3.5mm";"M023.5MM_LOCK";"SCREWTERMINAL-3.5MM-2_LOCK";"Standard 2-pin 0.1" header. Use with";"";"CONN-08399";"";"";"";
"JP4";"3.5mm";"M023.5MM_LOCK";"SCREWTERMINAL-3.5MM-2_LOCK";"Standard 2-pin 0.1" header. Use with";"";"CONN-08399";"";"";"";
"JP5";"USB-B";"USBPTH";"USB-B-PTH";"USB Connectors";"";"CONN-08278";"";"USB-B";"";
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
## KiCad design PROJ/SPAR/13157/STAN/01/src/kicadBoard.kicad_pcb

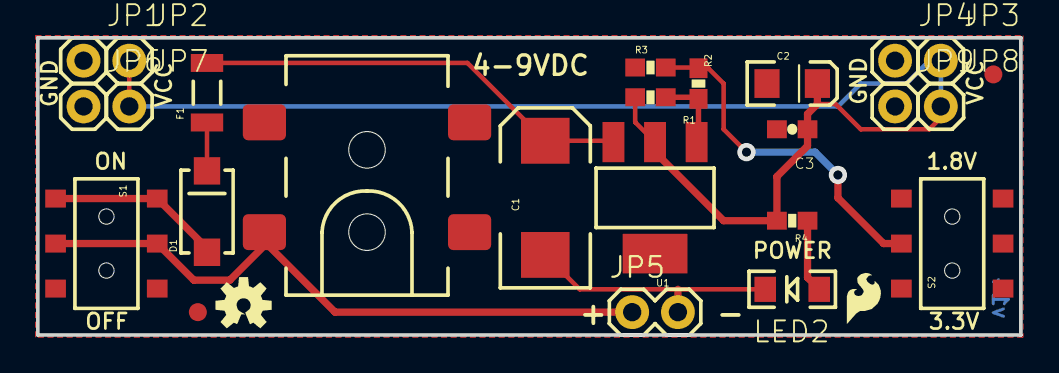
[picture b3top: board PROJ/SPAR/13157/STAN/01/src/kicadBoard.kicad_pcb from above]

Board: 2 copper layers, 54.6 x 16.5 mm, 29 parts (1 on the bottom side), 9 nets.

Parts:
C1: 100uF; EIA7343
C2: 10uF; EIA3216
C3: 0.1uF; 0603-CAP
D1: 1N4001; SMA-DIODE-TYLERALT1
F1: PTCSMD-W; PTC-1206-WIDE
FRAME1: FRAME-LETTER; CREATIVE_COMMONS
J1: POWER_JACKOVERPASTE_REDBOARD_0603; POWER_JACK_SMD_OVERPASTE_REDBOARD_0603
JP1, JP2, JP3, JP4, JP6, JP7, JP8, JP9: M01PTH; 1X01
JP5: 1X02
LED2: Power; LED-1206
LOGO1: OSHW-LOGOS; OSHW-LOGO-S
R1, R4: 240; 0603-RES
R2: 105; 0603-RES
R3: 287; 0603-RES
S1: On/Off; AYZ0202
S2: Voltage; AYZ0202
U1: V_REG_317SMD; SOT223
U$1: LOGO-SFESK; SFE-LOGO-FLAME
U$2: LOGO-SFENEW; SFE-NEW-WEBLOGO
U$3, U$4: FIDUCIAL1X2; FIDUCIAL-1X2

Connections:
GND: C1.C, C2.C, C3.2, J1.GND, J1.P$4, JP1.1, JP4.1, JP5.2, JP6.1, JP9.1, LED2.C, R3.1, S2.3
unnamed: D1.C, F1.1
unnamed: D1.A, S1.1, S1.4
unnamed: R2.1, R3.2, S2.2
unnamed: R1.1, R2.2, U1.1
unnamed: LED2.A, R4.1
RAW: C1.A, F1.2, U1.3
VCC: C2.A, C3.1, JP2.1, JP3.1, JP7.1, JP8.1, R1.2, R4.2, U1.2
VIN: J1.VIN0, JP5.1, S1.2, S1.5

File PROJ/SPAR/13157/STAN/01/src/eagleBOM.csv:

"Part";"Value";"Device";"Package";"Description";"PROD_ID";"VALUE";
"C1";"100uF";"CAP_POL7343";"EIA7343";"Capacitor Polarized";"";"";
"C2";"10uF";"CAP_POL1206";"EIA3216";"Capacitor Polarized";"";"";
"C3";"0.1uF";"CAP0603-CAP";"0603-CAP";"Capacitor";"";"";
"D1";"1N4001";"DIODESMA-TYLERALT1";"SMA-DIODE-TYLERALT1";"Diode";"";"";
"F1";"PTCSMD-W";"PTCSMD-W";"PTC-1206-WIDE";"Resettable Fuse PTC";"";"";
"FRAME1";"FRAME-LETTER";"FRAME-LETTER";"CREATIVE_COMMONS";"Schematic Frame";"";"";
"J1";"POWER_JACKOVERPASTE_REDBOARD_0603";"POWER_JACKOVERPASTE_REDBOARD_0603";"POWER_JACK_SMD_OVERPASTE_REDBOARD_0603";"Power Jack";"";"";
"JP1";"M01PTH";"M01PTH";"1X01";"Header 1";"";"";
"JP2";"M01PTH";"M01PTH";"1X01";"Header 1";"";"";
"JP3";"M01PTH";"M01PTH";"1X01";"Header 1";"";"";
"JP4";"M01PTH";"M01PTH";"1X01";"Header 1";"";"";
"JP5";"";"M02PTH";"1X02";"Header 2";"";"";
"JP6";"M01PTH";"M01PTH";"1X01";"Header 1";"";"";
"JP7";"M01PTH";"M01PTH";"1X01";"Header 1";"";"";
"JP8";"M01PTH";"M01PTH";"1X01";"Header 1";"";"";
"JP9";"M01PTH";"M01PTH";"1X01";"Header 1";"";"";
"LED2";"Power";"LED1206";"LED-1206";"";"";"";
"LOGO1";"OSHW-LOGOS";"OSHW-LOGOS";"OSHW-LOGO-S";"Open Source Hardware Logo This logo indicates the piece of hardware it is found on incorporates a OSHW license and/or adheres to the definition of open source hardware found here: http://freedomdefined.org/OSHW";"";"";
"R1";"240";"240OHM1/10W1%(0603)";"0603-RES";"RES-07849";"RES-07849";"240";
"R2";"105";"105OHM-1/10W-1%(0603)";"0603-RES";"RES-10751";"RES-10751";"105";
"R3";"287";"287OHM-1/10W-1%(0603)";"0603-RES";"RES-10752";"RES-10752";"287";
"R4";"240";"240OHM1/10W1%(0603)";"0603-RES";"RES-07849";"RES-07849";"240";
"S1";"On/Off";"AYZ0202";"AYZ0202";"SPDT Slide Switch";"";"";
"S2";"Voltage";"SWITCH-SPSTSMD";"AYZ0202";"SPST Switch";"";"";
"U$1";"LOGO-SFESK";"LOGO-SFESK";"SFE-LOGO-FLAME";"Spark Fun Electronics PCB Logo";"";"";
"U$2";"LOGO-SFENEW";"LOGO-SFENEW";"SFE-NEW-WEBLOGO";"Spark Fun Electronics PCB Logo";"";"";
"U$3";"FIDUCIAL1X2";"FIDUCIAL1X2";"FIDUCIAL-1X2";"Fiducial Alignment Points";"";"";
"U$4";"FIDUCIAL1X2";"FIDUCIAL1X2";"FIDUCIAL-1X2";"Fiducial Alignment Points";"";"";
"U1";"V_REG_317SMD";"V_REG_317SMD";"SOT223";"Voltage Regulator";"";"";

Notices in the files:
parts and their libraries:
RELEASED UNDER THE CREATIVE COMMONS ATTRIBUTION SHARE-ALIKE 4.0 LICENSE
HTTPS://CREATIVECOMMONS.ORG/LICENSES/BY-SA/4.0
HTTP://CREATIVECOMMONS.ORG/LICENSES/BY-SA/3.0
RELEASED UNDER THE CREATIVE COMMONS ATTRIBUTION SHARE-ALIKE 3.0 LICENSE
